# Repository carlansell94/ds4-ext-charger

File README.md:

A compact board that adds USB charging capability to the Dualshock 4's EXT port.

Features:
* Choice of either a micro USB or USB C port. (Combined version only)
* Includes pads for 5.1k&#937; resistors, to allow the use of 'smart' chargers (USB C only).
* No alteration to the outside of the controller is necessary.

A USB C only version of the board is also available, which removes the need to solder the jumper.

Included in this repository are the KiCAD files for this design. If you're only interested in having the board manufactured, gerbers are available under 'releases'.

Parts List:
* 1x 16 pin USB type C port/1x 5 pin micro USB port
* 2x 0603 5.1k&#937; resistors (optional)

For more information, take a look at [my blog post](https://qubitsandbytes.co.uk/post/dualshock-4-ext-port-charger).

## Images
Top:

Bottom:

## KiCAD
The files in this project were created using KiCAD 6, which introduced a new file format not compatible with older versions. Ensure you are using KiCAD 6 if you wish to open the files.

In addition, the USB Type C port pictured in the 3D render can be found [over here](https://github.com/ai03-2725/Type-C.pretty) - the file you're looking for is 'HRO TYPE-C-31-M-12.step'. It's not required, unless you want to see the part populated using the 3D viewer.

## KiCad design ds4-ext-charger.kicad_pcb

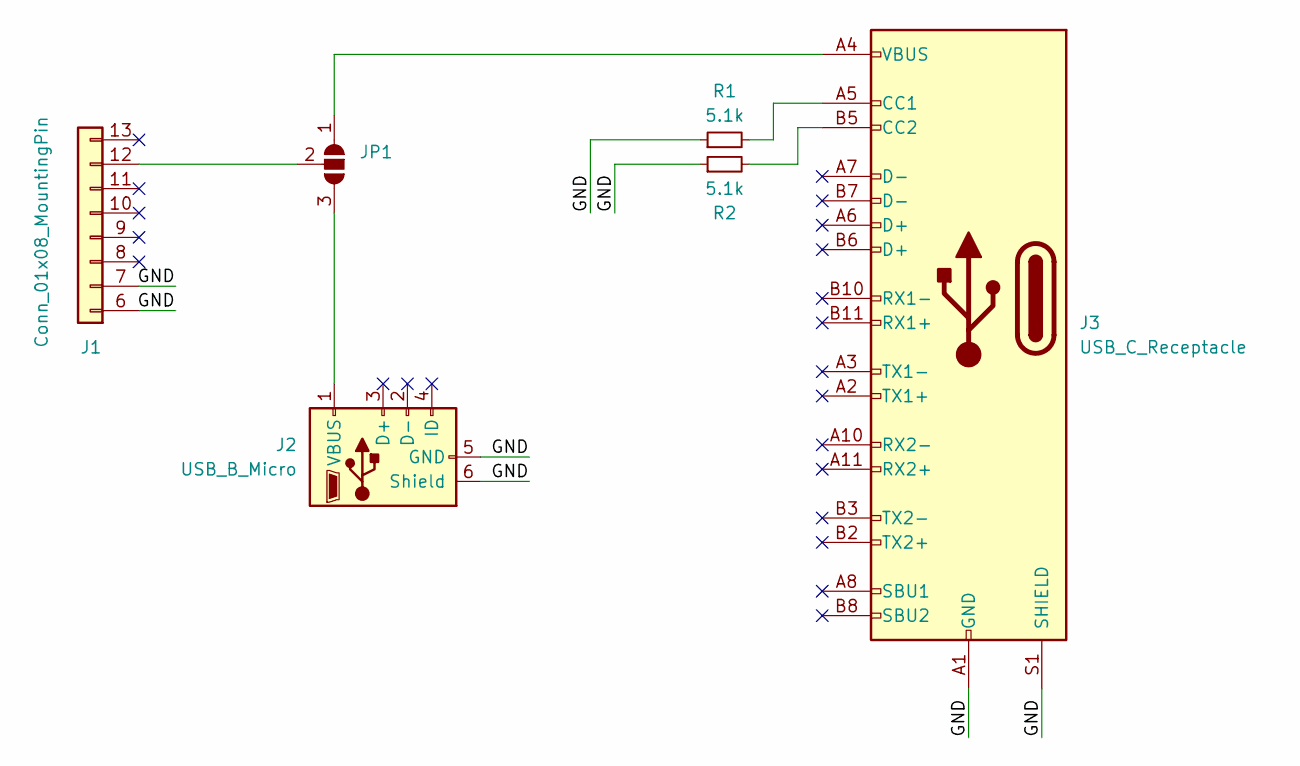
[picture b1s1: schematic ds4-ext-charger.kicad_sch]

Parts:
J1: Conn_01x08_MountingPin; PS4 EXT
J2: USB_B_Micro; USB_Micro-B_Amphenol_10118194_Horizontal
J3: USB_C_Receptacle; USB_C_Receptacle_HRO_TYPE-C-31-M-12
JP1: (no value)
R1, R2: 5.1k; R_0603_1608Metric

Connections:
/GND: J1.6 (Pin_1), J1.7 (Pin_2), J2.5 (GND), J2.6 (Shield), J3.A1 (GND), J3.A12 (GND), J3.B1 (GND), J3.B12 (GND), J3.S1 (SHIELD), R1.1, R2.1
unnamed: J1.12 (Pin_7), JP1.2 (C)
unnamed: J2.1 (VBUS), JP1.3 (B)
unnamed: J3.A4 (VBUS), J3.A9 (VBUS), J3.B4 (VBUS), J3.B9 (VBUS), JP1.1 (A)
unnamed: J3.A5 (CC1), R1.2
unnamed: J3.B5 (CC2), R2.2

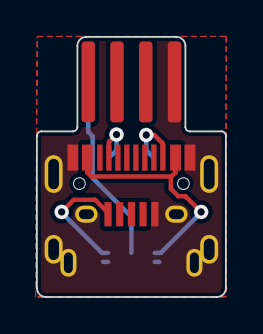
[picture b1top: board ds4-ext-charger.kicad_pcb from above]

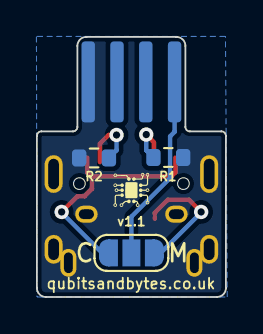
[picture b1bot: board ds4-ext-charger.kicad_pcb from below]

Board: 2 copper layers, 10.5 x 14.5 mm, 6 parts (3 on the bottom side), 6 nets.

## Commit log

2023-10-04 feat: Add separate USB C only version
2023-10-04 feat: Update to KiCAD v7 file format
